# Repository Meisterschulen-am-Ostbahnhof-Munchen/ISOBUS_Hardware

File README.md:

# ISOBUS Hardware

Welcome to the **ISOBUS Hardware** repository by **Meisterschulen am Ostbahnhof, München**. This repository hosts hardware designs for Open Source ISOBUS ECUs.

## 📂 Projects

### [Hutschienenmoped](./Hutschienenmoped)
The **Hutschienenmoped** is an Open Source ISOBUS ECU designed for DIN rail mounting.

* **📂 Source Code:** [View Directory](./Hutschienenmoped)
* **📖 Documentation:** [Read the Docs](https://install-isobus-environment-docs.readthedocs.io/de/latest/HutschienenMoped.html)

---

### [Hutschienenmoped XL](./Hutschienenmoped-XL)
The **Hutschienenmoped XL** is an extended version of the Open Source ISOBUS ECU.

* **📂 Source Code:** [View Directory](./Hutschienenmoped-XL)
* **🏅 Open Hardware:** Certified under [DE000145](https://certification.oshwa.org/de000145.html)

## 📜 License

This project is licensed under a **Creative Commons Attribution-ShareAlike 4.0 International License (CC BY-SA 4.0)**.

* **Hutschienenmoped** by Meisterschulen am Ostbahnhof, München
* **ISOBUS_Hardware** by Meisterschulen am Ostbahnhof, München

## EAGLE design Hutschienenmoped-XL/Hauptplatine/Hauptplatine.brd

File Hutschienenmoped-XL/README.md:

# Hutschienenmoped XL

Das **Hutschienenmoped XL** ist ein innovatives Gerät, das speziell für die Integration in ISOBUS-Systeme entwickelt wurde. Es handelt sich dabei um eine Open-Source-ECU (Electronic Control Unit), die mit den Standards **ISO 11783** und **IEC 61499** kompatibel ist. Diese Kompatibilität ermöglicht eine nahtlose Kommunikation und Steuerung von landwirtschaftlichen Maschinen und Anbaugeräten.

### Vorteile
* **Flexibilität:** Durch die Open-Source-Natur des Projekts können Benutzer die Software und Hardware nach ihren Bedürfnissen anpassen und erweitern.
* **Kompatibilität:** Es unterstützt eine Vielzahl von ISOBUS-kompatiblen Geräten, was die Integration in bestehende Systeme erleichtert.
* **Zukunftssicherheit:** Dank der Einhaltung internationaler Standards ist das Gerät zukunftssicher und kann in verschiedenen landwirtschaftlichen Anwendungen eingesetzt werden.

---

## 🛠 CAD & 3D-Design (Fusion 360)

Das Projekt wird derzeit in Fusion 360 migriert. Hier finden Sie die aktuellen Modelle:

* 🔌 **[Hauptplatine (PCB)](https://a360.co/3YcFeBx)**
* 📦 **[Zusammenbau (Assembly)](https://a360.co/4cJ5Ajy)**

### Galerie

---

## 📜 Lizenz

Dieses Projekt ist lizenziert unter einer **Creative Commons Attribution-ShareAlike 4.0 International License (CC BY-SA 4.0)**.

* **Urheber:** [Meisterschulen am Ostbahnhof, München](https://github.com/Meisterschulen-am-Ostbahnhof-Munchen)
* **Projekt:** [Hutschienenmoped](https://github.com/Meisterschulen-am-Ostbahnhof-Munchen/ISOBUS_Hardware)

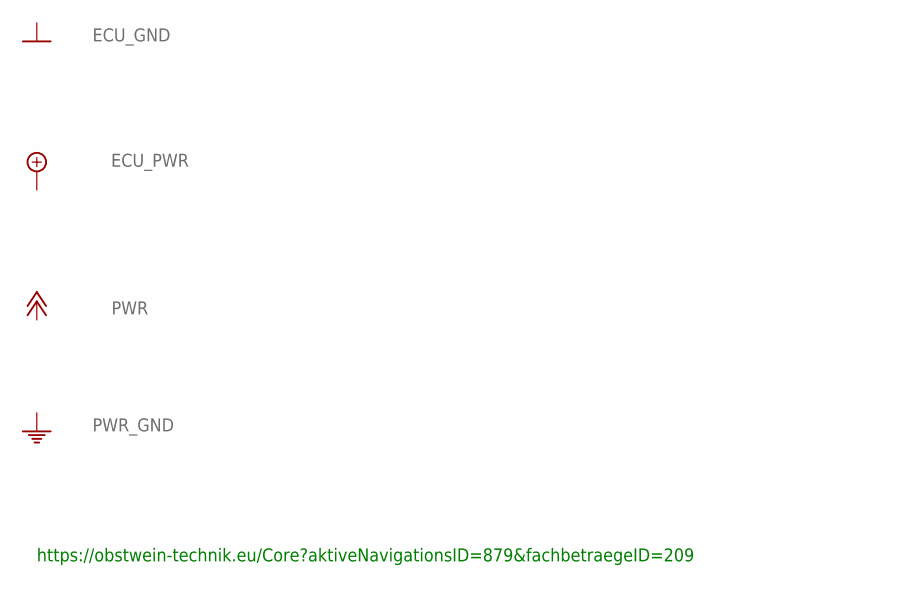
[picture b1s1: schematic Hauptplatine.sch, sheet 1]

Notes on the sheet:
https://obstwein-technik.eu/Core?aktiveNavigationsID=879&fachbetraegeID=209

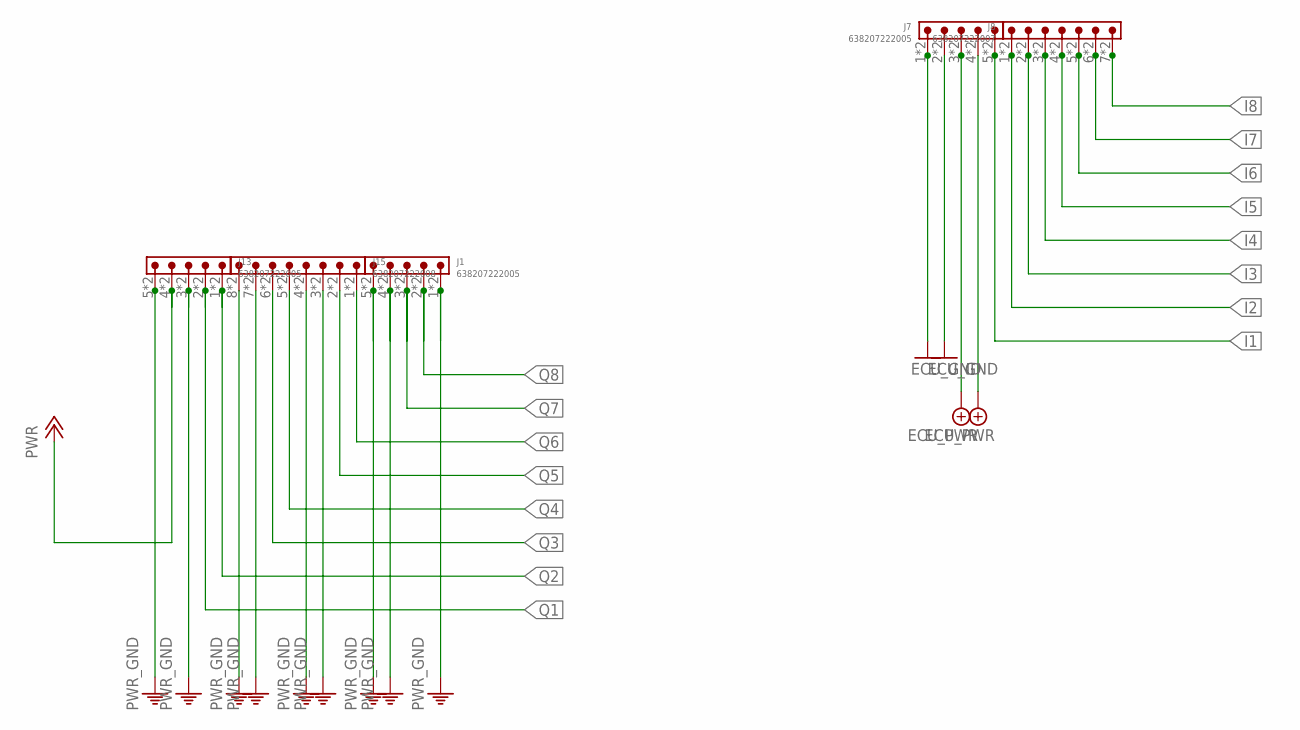
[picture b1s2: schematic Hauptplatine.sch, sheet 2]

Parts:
J1, J7, J13: 638207222005
J8: 638207222007
J15: 638207222008

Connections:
ECU_GND: J7.1, J7.2, J7.A1 (1), J7.A2 (2); also elsewhere on the board
ECU_PWR: J7.3, J7.4, J7.A3 (3), J7.A4 (4); also elsewhere on the board
I1: J7.5, J7.A5 (5); also elsewhere on the board
I2: J8.1, J8.A1 (1); also elsewhere on the board
I3: J8.2, J8.A2 (2); also elsewhere on the board
I4: J8.3, J8.A3 (3); also elsewhere on the board
I5: J8.4, J8.A4 (4); also elsewhere on the board
I6: J8.5, J8.A5 (5); also elsewhere on the board
I7: J8.6, J8.A6 (6); also elsewhere on the board
I8: J8.7, J8.A7 (7); also elsewhere on the board
PWR: J13.4, J13.A4 (4); also elsewhere on the board
PWR_GND: J1.1, J1.4, J1.5, J1.A1 (1), J1.A4 (4), J1.A5 (5), J13.3, J13.5, J13.A3 (3), J13.A5 (5), J15.3, J15.4, J15.7, J15.8, J15.A3 (3), J15.A4 (4), J15.A7 (7), J15.A8 (8); also elsewhere on the board
Q1: J13.2, J13.A2 (2); also elsewhere on the board
Q2: J13.1, J13.A1 (1); also elsewhere on the board
Q3: J15.6, J15.A6 (6); also elsewhere on the board
Q4: J15.5, J15.A5 (5); also elsewhere on the board
Q5: J15.2, J15.A2 (2); also elsewhere on the board
Q6: J15.1, J15.A1 (1); also elsewhere on the board
Q7: J1.3, J1.A3 (3); also elsewhere on the board
Q8: J1.2, J1.A2 (2); also elsewhere on the board

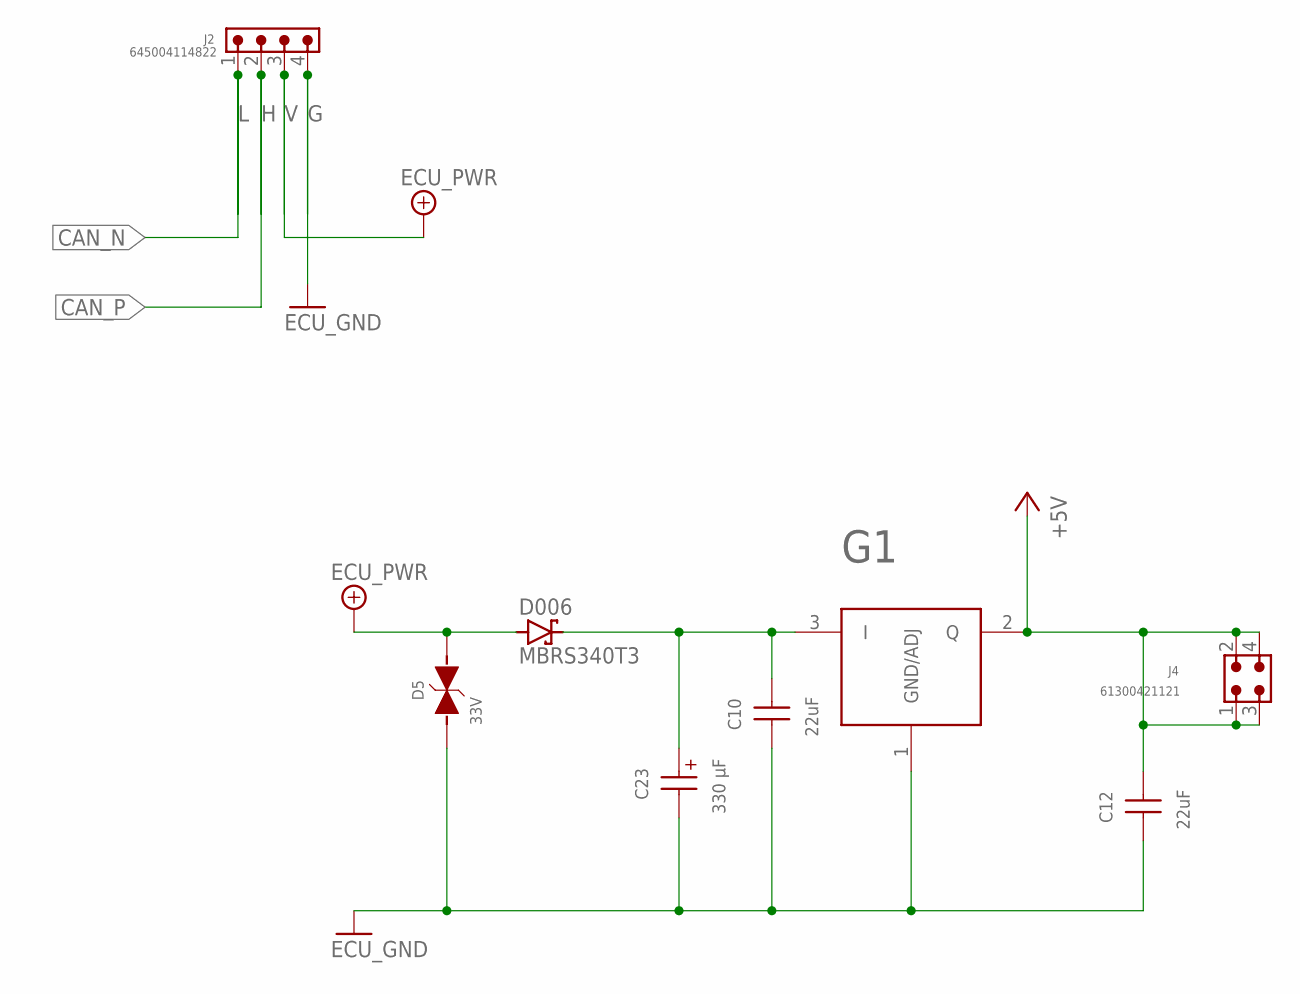
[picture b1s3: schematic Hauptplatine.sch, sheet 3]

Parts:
C10: 22uF; WCAP-CSGP_1210_H2.5
C12: 22uF; WCAP-CSGP_0805_H1.25_R
C23: 330 µF; WCAP-ASLI_12.5X14(DXL)
D5: 33V; WE-TVSP_DO-214AB_BIDIRECTIONAL
D006: MBRS340T3; SMC
G1: IFX27001TF_V50; INF-PG-TO252-3-11_N
J2: 645004114822
J4: 61300421121

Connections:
+5V: C12.2, G1.2 (Q), J4.1, J4.2, J4.3, J4.4; also elsewhere on the board
CAN_N: J2.1; also elsewhere on the board
CAN_P: J2.2; also elsewhere on the board
ECU_GND: C10.1, C12.1, C23.2 (-), D5.1, G1.1 (GND/ADJ), J2.4; also elsewhere on the board
ECU_PWR: D5.2, D006.A, J2.3; also elsewhere on the board
unnamed: C10.2, C23.1 (+), D006.C, G1.3 (I)

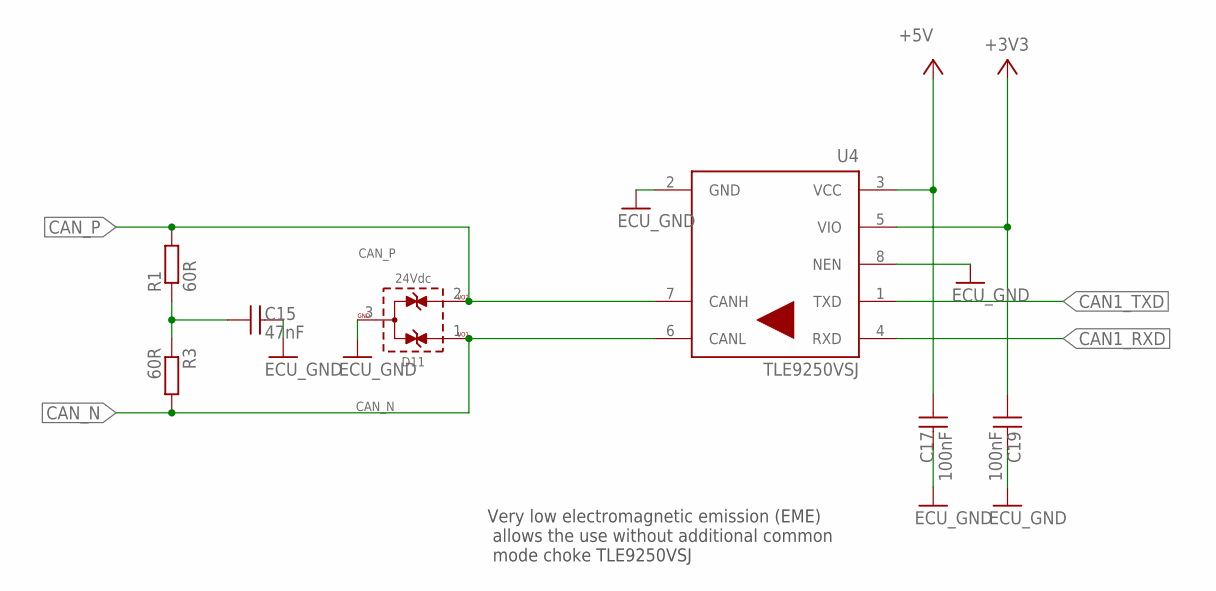
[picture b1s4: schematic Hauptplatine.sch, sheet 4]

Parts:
C15: 47nF; WCAP-CSGP_0805_H0.8_R
C17, C19: 100nF; WCAP-CSGP_0805_H0.8_R
D11: 24Vdc; WE-TVS_SOT23-3L
R1, R3: 60R; R0805
U4: TLE9250VSJ; SOIC127P602X173-8N-V

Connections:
+3V3: C19.1, U4.5 (VIO); also elsewhere on the board
+5V: C17.1, U4.3 (VCC); also elsewhere on the board
CAN1_RXD: U4.4 (RXD); also elsewhere on the board
CAN1_TXD: U4.1 (TXD); also elsewhere on the board
CAN_N: D11.1 (I/O1), R3.2, U4.6 (CANL); also elsewhere on the board
CAN_P: D11.2 (I/O2), R1.2, U4.7 (CANH); also elsewhere on the board
ECU_GND: C15.2, C17.2, C19.2, D11.3 (GND), U4.2 (GND), U4.8 (NEN); also elsewhere on the board
unnamed: C15.1, R1.1, R3.1

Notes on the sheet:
Very low electromagnetic emission (EME) allows the use without additional common mode choke TLE9250VSJ

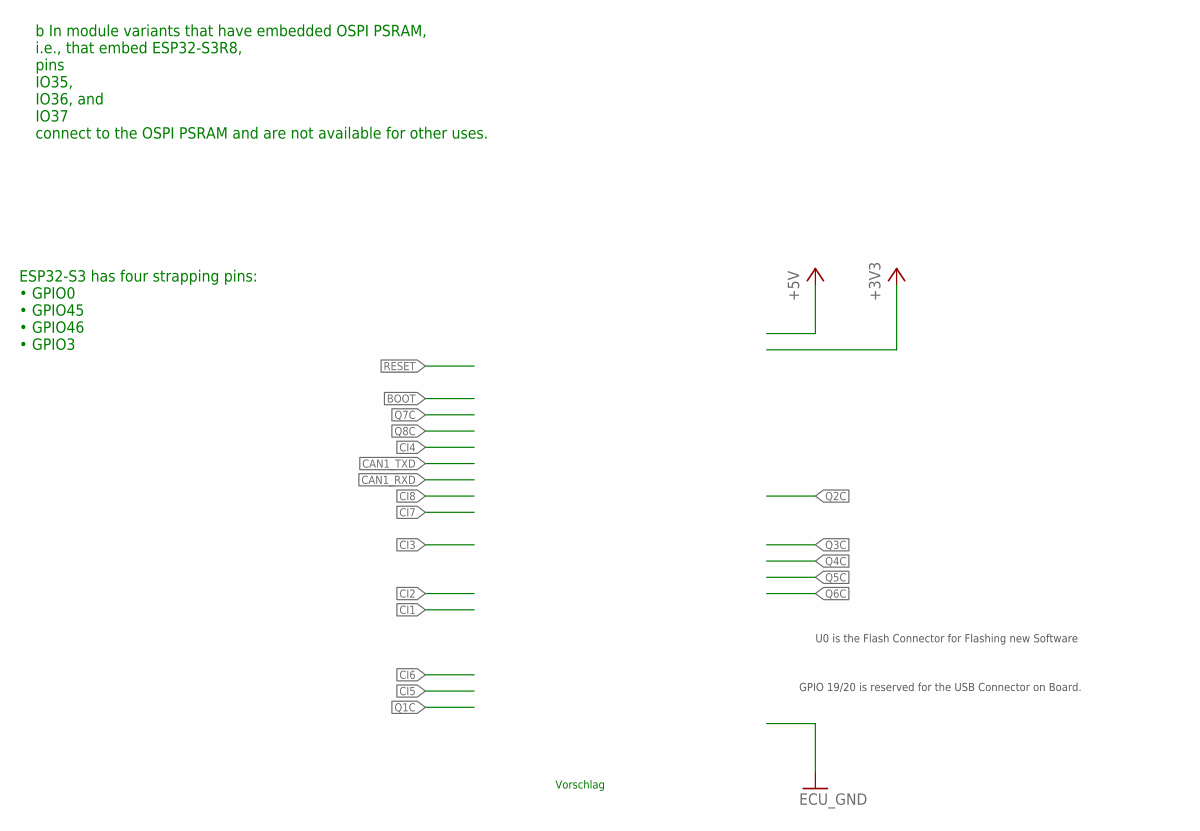
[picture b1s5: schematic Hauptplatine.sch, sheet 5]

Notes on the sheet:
Vorschlag
ESP32-S3 has four strapping pins: • GPIO0 • GPIO45 • GPIO46 • GPIO3
b In module variants that have embedded OSPI PSRAM, i.e., that embed ESP32-S3R8, pins IO35, IO36, and IO37 connect to the OSPI PSRAM and are not available for other uses.
GPIO 19/20 is reserved for the USB Connector on Board.
U0 is the Flash Connector for Flashing new Software

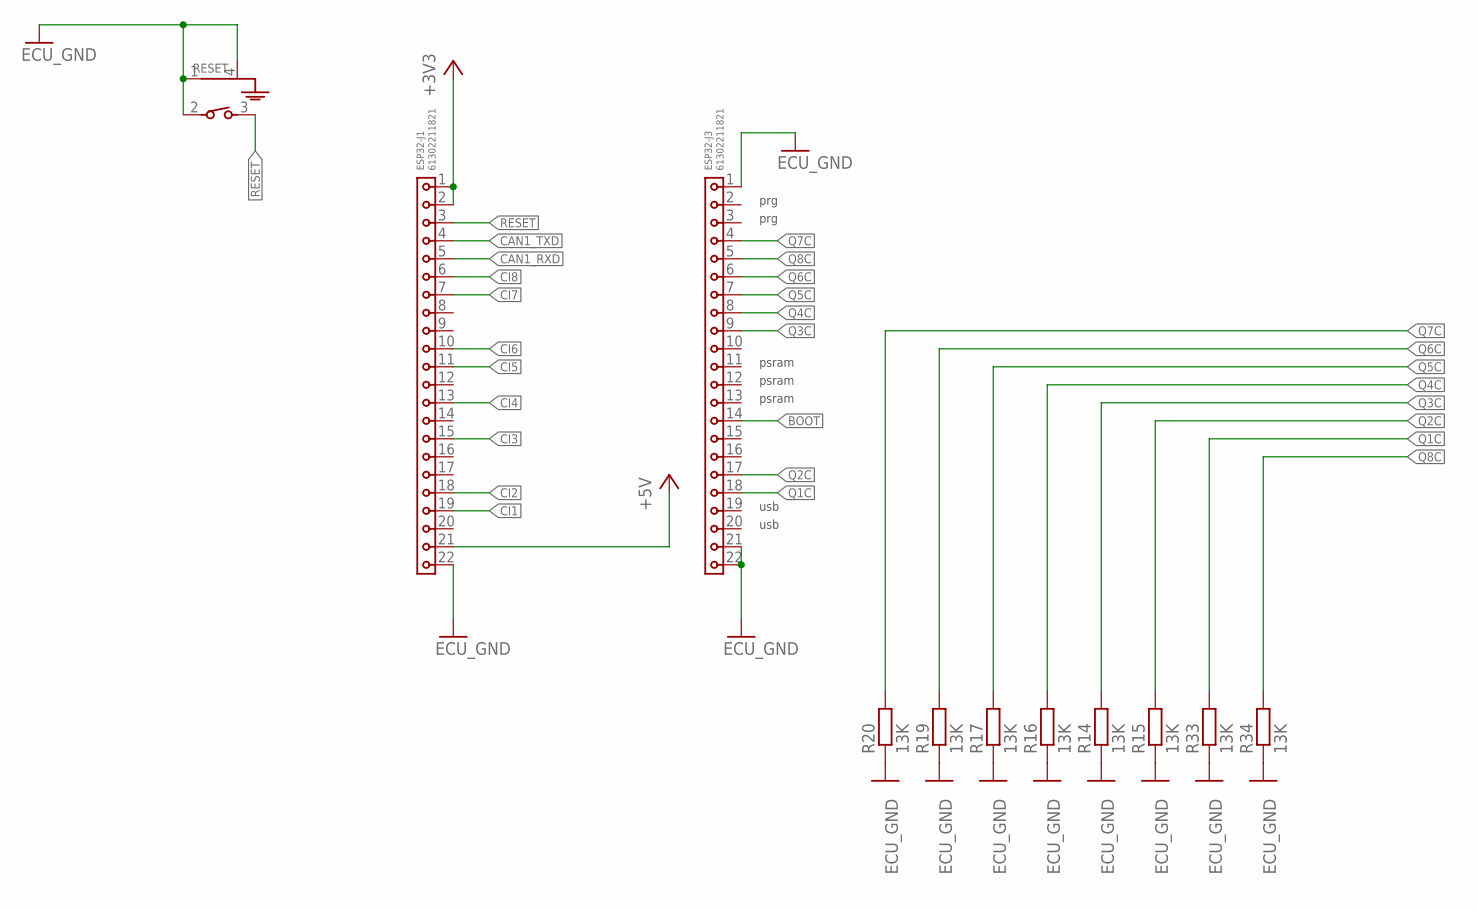
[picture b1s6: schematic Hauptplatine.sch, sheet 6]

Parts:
ESP32-J1, ESP32-J3: 61302211821
R14, R15, R16, R17, R19, R20, R33, R34: 13K; R1206
RESET: 431256083736; 4312560837X6

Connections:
+3V3: ESP32-J1.1, ESP32-J1.2; also elsewhere on the board
+5V: ESP32-J1.21; also elsewhere on the board
BOOT: ESP32-J3.14
CAN1_RXD: ESP32-J1.5; also elsewhere on the board
CAN1_TXD: ESP32-J1.4; also elsewhere on the board
CI1: ESP32-J1.19; also elsewhere on the board
CI2: ESP32-J1.18; also elsewhere on the board
CI3: ESP32-J1.15; also elsewhere on the board
CI4: ESP32-J1.13; also elsewhere on the board
CI5: ESP32-J1.11; also elsewhere on the board
CI6: ESP32-J1.10; also elsewhere on the board
CI7: ESP32-J1.7; also elsewhere on the board
CI8: ESP32-J1.6; also elsewhere on the board
ECU_GND: ESP32-J1.22, ESP32-J3.1, ESP32-J3.21, ESP32-J3.22, R14.1, R15.1, R16.1, R17.1, R19.1, R20.1, R33.1, R34.1, RESET.1 (GND1), RESET.2, RESET.4 (GND); also elsewhere on the board
Q1C: ESP32-J3.18, R33.2; also elsewhere on the board
Q2C: ESP32-J3.17, R15.2; also elsewhere on the board
Q3C: ESP32-J3.9, R14.2; also elsewhere on the board
Q4C: ESP32-J3.8, R16.2; also elsewhere on the board
Q5C: ESP32-J3.7, R17.2; also elsewhere on the board
Q6C: ESP32-J3.6, R19.2; also elsewhere on the board
Q7C: ESP32-J3.4, R20.2; also elsewhere on the board
Q8C: ESP32-J3.5, R34.2; also elsewhere on the board
RESET: ESP32-J1.3, RESET.3

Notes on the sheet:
usb
prg
psram

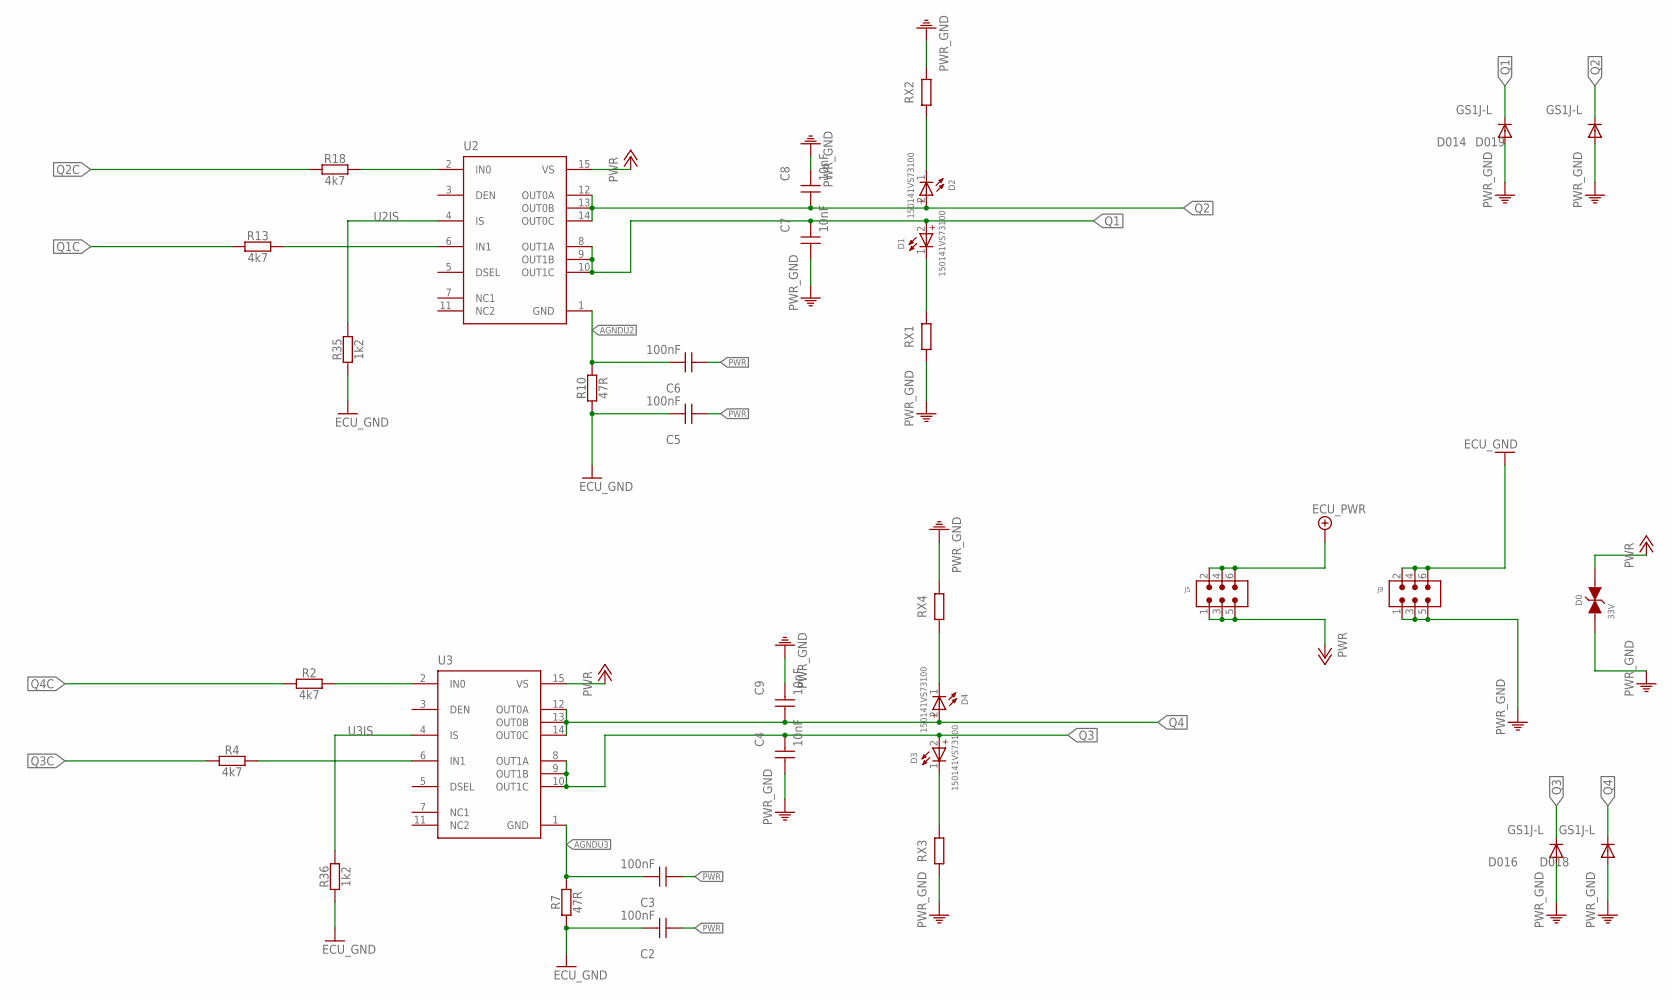
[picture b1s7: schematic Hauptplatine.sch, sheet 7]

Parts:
C2, C3, C5, C6: 100nF; WCAP-CSGP_0805_H0.8_R
C4, C7, C8, C9: 10nF; WCAP-CSGP_0805_H0.8_R
D0: 33V; WE-TVSP_DO-214AB_BIDIRECTIONAL
D1, D2, D3, D4: 150141VS73100; WL-SMTW_3528
D014, D016, D018, D019: GS1J-L; SMA_DO-214AC
J5, J9: 6130XX21121_61300621121; 61300621121
R2, R4, R13, R18: 4k7; R0805
R7, R10: 47R; R0805
R35, R36: 1k2; R0805
RX1, RX2, RX3, RX4: 470Ohm; R1206
U2, U3: BTS7030-2EPA; SOP65P600X115-15N-V

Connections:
AGNDU2: C6.2, R10.2, U2.1 (GND)
AGNDU3: C3.2, R7.2, U3.1 (GND)
ECU_GND: C2.2, C5.2, J9.2, J9.4, J9.6, R7.1, R10.1, R35.1, R36.1; also elsewhere on the board
ECU_PWR: J5.2, J5.4, J5.6; also elsewhere on the board
unnamed: D4.1 (-), RX4.1
unnamed: R2.2, U3.2 (IN0)
unnamed: R4.2, U3.6 (IN1)
unnamed: D2.1 (-), RX2.1
unnamed: D1.1 (-), RX1.2
unnamed: D3.1 (-), RX3.2
unnamed: R18.2, U2.2 (IN0)
unnamed: R13.2, U2.6 (IN1)
PWR: C2.1, C3.1, C5.1, C6.1, D0.2, J5.1, J5.3, J5.5, U2.15 (VS), U3.15 (VS); also elsewhere on the board
PWR_GND: C4.1, C7.1, C8.2, C9.2, D0.1, D014.A, D016.A, D018.A, D019.A, J9.1, J9.3, J9.5, RX1.1, RX2.2, RX3.1, RX4.2; also elsewhere on the board
Q1: C7.2, D1.2 (+), D014.C, U2.8 (OUT1A), U2.9 (OUT1B), U2.10 (OUT1C); also elsewhere on the board
Q1C: R13.1; also elsewhere on the board
Q2: C8.1, D2.2 (+), D019.C, U2.12 (OUT0A), U2.13 (OUT0B), U2.14 (OUT0C); also elsewhere on the board
Q2C: R18.1; also elsewhere on the board
Q3: C4.2, D3.2 (+), D016.C, U3.8 (OUT1A), U3.9 (OUT1B), U3.10 (OUT1C); also elsewhere on the board
Q3C: R4.1; also elsewhere on the board
Q4: C9.1, D4.2 (+), D018.C, U3.12 (OUT0A), U3.13 (OUT0B), U3.14 (OUT0C); also elsewhere on the board
Q4C: R2.1; also elsewhere on the board
U2IS: R35.2, U2.4 (IS)
U3IS: R36.2, U3.4 (IS)

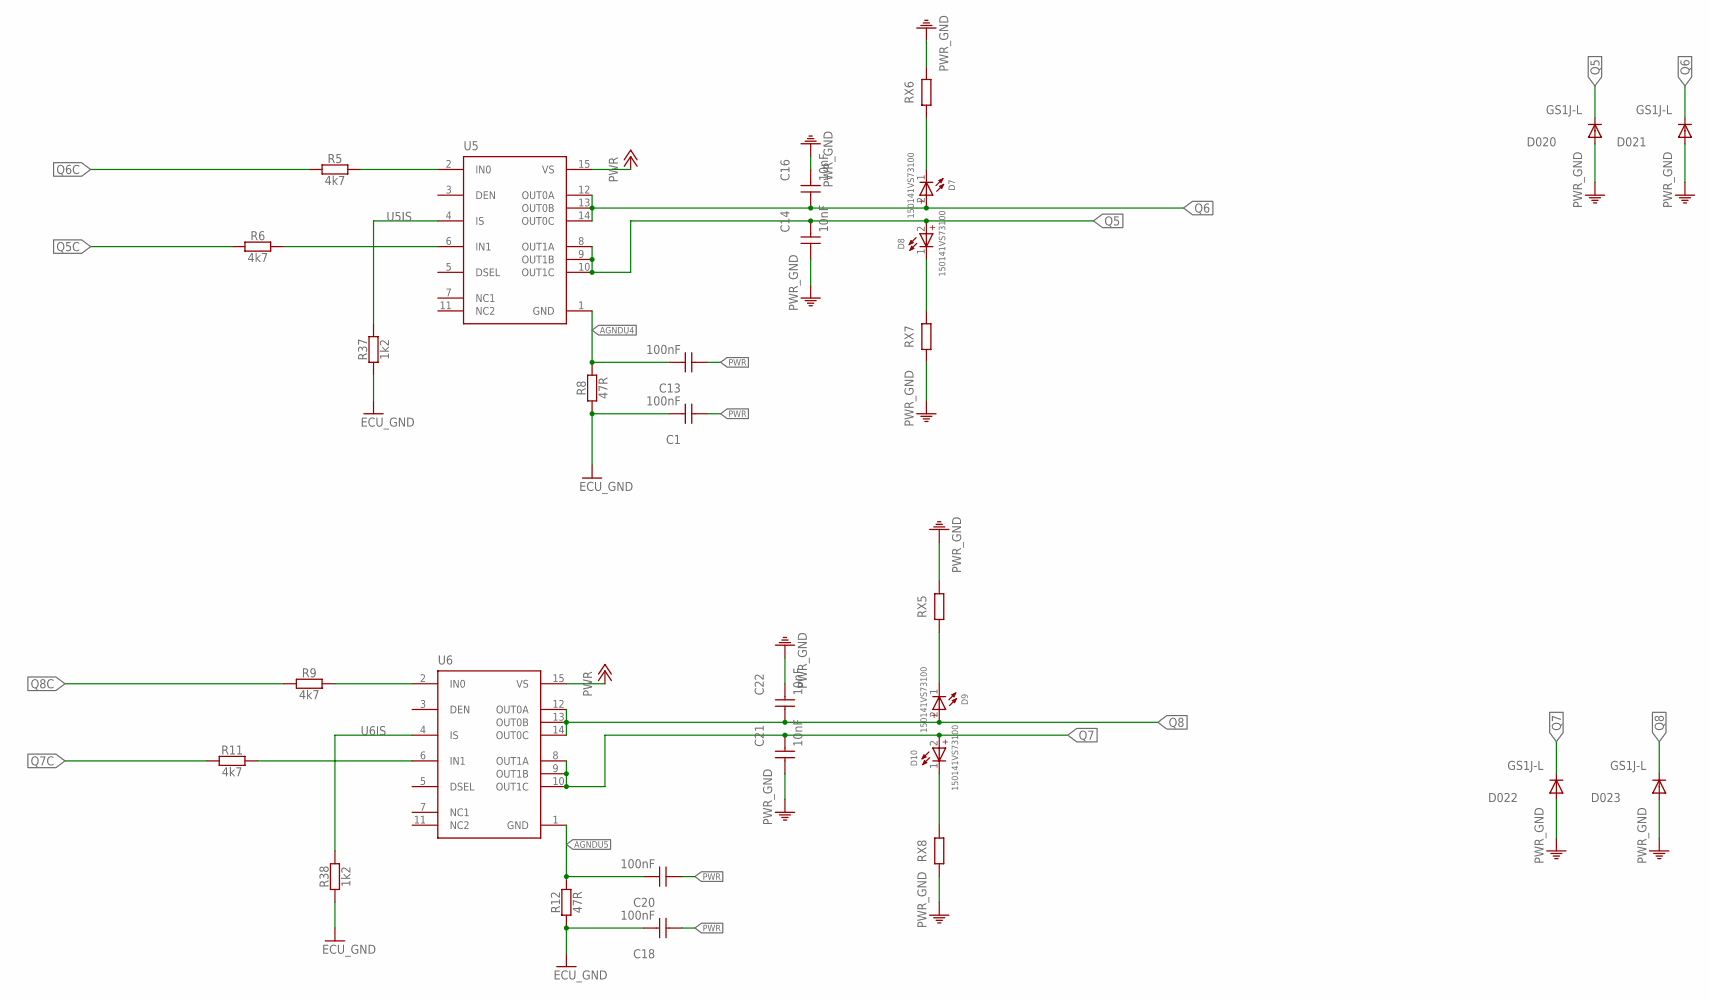
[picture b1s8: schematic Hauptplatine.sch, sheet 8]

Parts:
C1, C13, C18, C20: 100nF; WCAP-CSGP_0805_H0.8_R
C14, C16, C21, C22: 10nF; WCAP-CSGP_0805_H0.8_R
D7, D8, D9, D10: 150141VS73100; WL-SMTW_3528
D020, D021, D022, D023: GS1J-L; SMA_DO-214AC
R5, R6, R9, R11: 4k7; R0805
R8, R12: 47R; R0805
R37, R38: 1k2; R0805
RX5, RX6, RX7, RX8: 470Ohm; R1206
U5, U6: BTS7030-2EPA; SOP65P600X115-15N-V

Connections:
+6V: D7.1 (-), RX6.1
AGNDU4: C13.2, R8.2, U5.1 (GND)
AGNDU5: C20.2, R12.2, U6.1 (GND)
ECU_GND: C1.2, C18.2, R8.1, R12.1, R37.1, R38.1; also elsewhere on the board
unnamed: R5.2, U5.2 (IN0)
unnamed: R6.2, U5.6 (IN1)
unnamed: R9.2, U6.2 (IN0)
unnamed: R11.2, U6.6 (IN1)
unnamed: D9.1 (-), RX5.1
unnamed: D8.1 (-), RX7.2
unnamed: D10.1 (-), RX8.2
PWR: C1.1, C13.1, C18.1, C20.1, U5.15 (VS), U6.15 (VS); also elsewhere on the board
PWR_GND: C14.1, C16.2, C21.1, C22.2, D020.A, D021.A, D022.A, D023.A, RX5.2, RX6.2, RX7.1, RX8.1; also elsewhere on the board
Q5: C14.2, D8.2 (+), D020.C, U5.8 (OUT1A), U5.9 (OUT1B), U5.10 (OUT1C); also elsewhere on the board
Q5C: R6.1; also elsewhere on the board
Q6: C16.1, D7.2 (+), D021.C, U5.12 (OUT0A), U5.13 (OUT0B), U5.14 (OUT0C); also elsewhere on the board
Q6C: R5.1; also elsewhere on the board
Q7: C21.2, D10.2 (+), D022.C, U6.8 (OUT1A), U6.9 (OUT1B), U6.10 (OUT1C); also elsewhere on the board
Q7C: R11.1; also elsewhere on the board
Q8: C22.1, D9.2 (+), D023.C, U6.12 (OUT0A), U6.13 (OUT0B), U6.14 (OUT0C); also elsewhere on the board
Q8C: R9.1; also elsewhere on the board
U5IS: R37.2, U5.4 (IS)
U6IS: R38.2, U6.4 (IS)

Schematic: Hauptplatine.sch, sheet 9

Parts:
C31, C32, C33, C34: 100nF; WCAP-CSGP_1206_H0.8
D13: 3.3Vdc; WE-TVS_SOT143-4L
R21, R24: 1K2; R1206
R22, R25: 47K; R1206
R23, R26: 22K; R1206

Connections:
+3V3: D13.4 (VDD); also elsewhere on the board
CI1: C32.1, D13.3 (2), R22.1, R23.2; also elsewhere on the board
CI2: C34.1, D13.2 (1), R25.1, R26.2; also elsewhere on the board
ECU_GND: C31.2, C32.2, C33.2, C34.2, D13.1 (GND), R21.1, R23.1, R24.1, R26.1; also elsewhere on the board
I1: C31.1, R21.2, R22.2; also elsewhere on the board
I2: C33.1, R24.2, R25.2; also elsewhere on the board

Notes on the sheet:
Symbol Parameter Min Typ Max Unit CIN Pin capacitance - 2 - pF VIH High-level input voltage 0.75×VDD1 - VDD1+0.3 V (‭2,475‬V - 3.6V) VIL Low-level input voltage –0.3 - 0.25×VDD1 V (-0,3 - ‭0,825‬V)
2.6V bei 12V 3.07 bei 14.2V

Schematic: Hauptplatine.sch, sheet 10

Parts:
C39, C40, C41, C42: 100nF; WCAP-CSGP_1206_H0.8
D15: 3.3Vdc; WE-TVS_SOT143-4L
R39, R42: 1K2; R1206
R40, R43: 47K; R1206
R41, R44: 22K; R1206

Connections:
+3V3: D15.4 (VDD); also elsewhere on the board
CI3: C40.1, D15.3 (2), R40.1, R41.2; also elsewhere on the board
CI4: C42.1, D15.2 (1), R43.1, R44.2; also elsewhere on the board
ECU_GND: C39.2, C40.2, C41.2, C42.2, D15.1 (GND), R39.1, R41.1, R42.1, R44.1; also elsewhere on the board
I3: C39.1, R39.2, R40.2; also elsewhere on the board
I4: C41.1, R42.2, R43.2; also elsewhere on the board

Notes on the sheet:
Symbol Parameter Min Typ Max Unit CIN Pin capacitance - 2 - pF VIH High-level input voltage 0.75×VDD1 - VDD1+0.3 V (‭2,475‬V - 3.6V) VIL Low-level input voltage –0.3 - 0.25×VDD1 V (-0,3 - ‭0,825‬V)
2.6V bei 12V 3.07 bei 14.2V

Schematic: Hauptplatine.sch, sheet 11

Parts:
C47, C48, C49, C50: 100nF; WCAP-CSGP_1206_H0.8
D17: 3.3Vdc; WE-TVS_SOT143-4L
R51, R54: 1K2; R1206
R52, R55: 47K; R1206
R53, R56: 22K; R1206

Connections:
+3V3: D17.4 (VDD); also elsewhere on the board
CI5: C48.1, D17.3 (2), R52.1, R53.2; also elsewhere on the board
CI6: C50.1, D17.2 (1), R55.1, R56.2; also elsewhere on the board
ECU_GND: C47.2, C48.2, C49.2, C50.2, D17.1 (GND), R51.1, R53.1, R54.1, R56.1; also elsewhere on the board
I5: C47.1, R51.2, R52.2; also elsewhere on the board
I6: C49.1, R54.2, R55.2; also elsewhere on the board

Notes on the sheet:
Symbol Parameter Min Typ Max Unit CIN Pin capacitance - 2 - pF VIH High-level input voltage 0.75×VDD1 - VDD1+0.3 V (‭2,475‬V - 3.6V) VIL Low-level input voltage –0.3 - 0.25×VDD1 V (-0,3 - ‭0,825‬V)
2.6V bei 12V 3.07 bei 14.2V

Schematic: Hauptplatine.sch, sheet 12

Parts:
C24, C25, C26, C27: 100nF; WCAP-CSGP_1206_H0.8
D12: 3.3Vdc; WE-TVS_SOT143-4L
R27, R28: 1K2; R1206
R29, R30: 47K; R1206
R31, R32: 22K; R1206

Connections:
+3V3: D12.4 (VDD); also elsewhere on the board
CI7: C27.1, D12.3 (2), R30.1, R32.2; also elsewhere on the board
CI8: C26.1, D12.2 (1), R29.1, R31.2; also elsewhere on the board
ECU_GND: C24.2, C25.2, C26.2, C27.2, D12.1 (GND), R27.1, R28.1, R31.1, R32.1; also elsewhere on the board
I7: C25.1, R28.2, R30.2; also elsewhere on the board
I8: C24.1, R27.2, R29.2; also elsewhere on the board

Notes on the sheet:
Symbol Parameter Min Typ Max Unit CIN Pin capacitance - 2 - pF VIH High-level input voltage 0.75×VDD1 - VDD1+0.3 V (‭2,475‬V - 3.6V) VIL Low-level input voltage –0.3 - 0.25×VDD1 V (-0,3 - ‭0,825‬V)
2.6V bei 12V 3.07 bei 14.2V

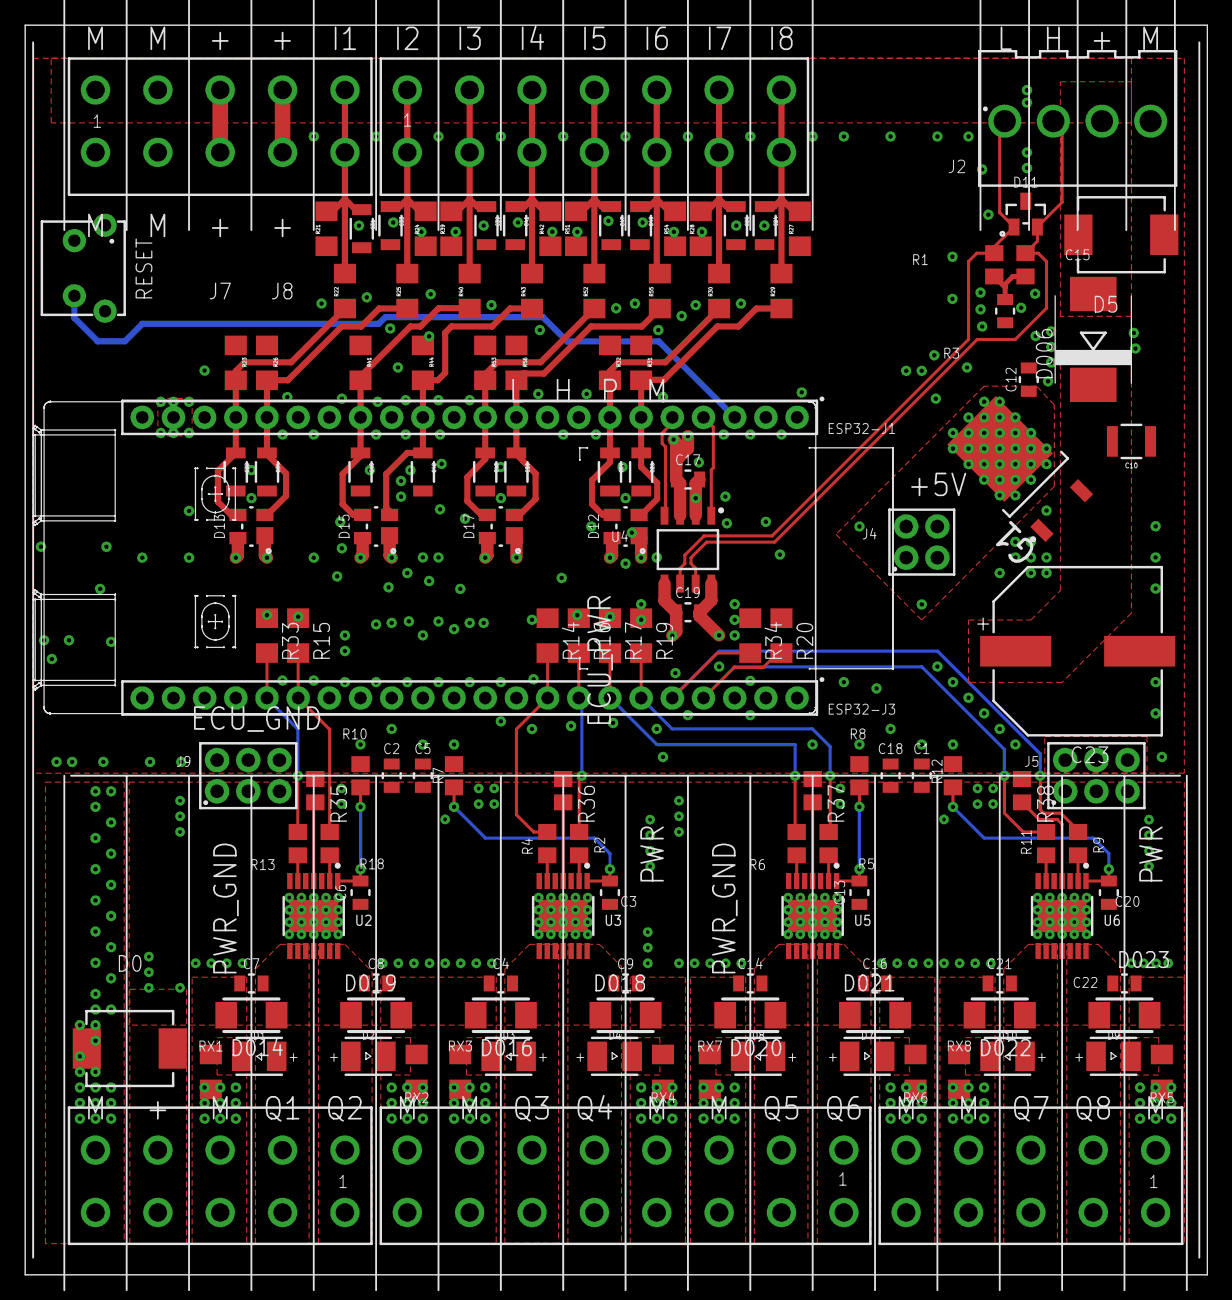
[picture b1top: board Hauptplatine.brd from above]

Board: 4 copper layers, 96.3 x 101.8 mm, 138 parts (0 on the bottom side), 69 nets.

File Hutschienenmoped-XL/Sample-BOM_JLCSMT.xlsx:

Comment | Designator | Footprint | JLCPCB Part #（optional）
431256083736 | RESET | 4312560837X6
6130XX21121_61300621121 | J5, J9 | 61300621121
BTS7030-2EPA | U2, U3, U5, U6 | SOP65P600X115-15N-V
IFX27001TF_V50 | G1 | INF-PG-TO252-3-11_N
61300421121 | J4 | 61300421121
61302211821 | ESP32-J1, ESP32-J3 | 61302211821
638207222005 | J1, J7, J13 | 638207222005
638207222007 | J8 | 638207222007
638207222008 | J15 | 638207222008
100nF | C1, C2, C3, C5, C6, C13, C17, C18, C19, C20 | WCAP-CSGP_0805_H0.8_R
100nF | C24, C25, C26, C27, C31, C32, C33, C34, C39, C40, C41, C42, C47, C48, C49, C50 | WCAP-CSGP_1206_H0.8
10nF | C4, C7, C8, C9, C14, C16, C21, C22 | WCAP-CSGP_0805_H0.8_R
13K | R14, R15, R16, R17, R19, R20, R23, R26, R31, R32, R33, R34, R41, R44, R53, R56 | R1206
150141VS73100 | D1, D2, D3, D4, D7, D8, D9, D10 | WL-SMTW_3528
1K2 | R21, R24, R27, R28, R39, R42, R51, R54 | R1206
1k2 | R35, R36, R37, R38 | R0805
22uF | C12 | WCAP-CSGP_0805_H1.25_R
22uF | C10 | WCAP-CSGP_1210_H2.5
24Vdc | D11 | WE-TVS_SOT23-3L
3.3Vdc | D12, D13, D15, D17 | WE-TVS_SOT143-4L
330 ÂµF | C23 | WCAP-ASLI_12.5X14(DXL)
33V | D0, D5 | WE-TVSP_DO-214AB_BIDIRECTIONAL
470Ohm | RX1, RX2, RX3, RX4, RX5, RX6, RX7, RX8 | R1206
47K | R22, R25, R29, R30, R40, R43, R52, R55 | R1206
47R | R7, R8, R10, R12 | R0805
47nF | C15 | WCAP-CSGP_0805_H0.8_R
4k7 | R2, R4, R5, R6, R9, R11, R13, R18 | R0805
60R | R1, R3 | R0805
645004114822 | J2 | 645004114822
GS1J-L | D014, D016, D018, D019, D020, D021, D022, D023 | SMA_DO-214AC
MBRS340T3 | D006 | SMC
TLE9250VSJ | U4 | SOIC127P602X173-8N-V

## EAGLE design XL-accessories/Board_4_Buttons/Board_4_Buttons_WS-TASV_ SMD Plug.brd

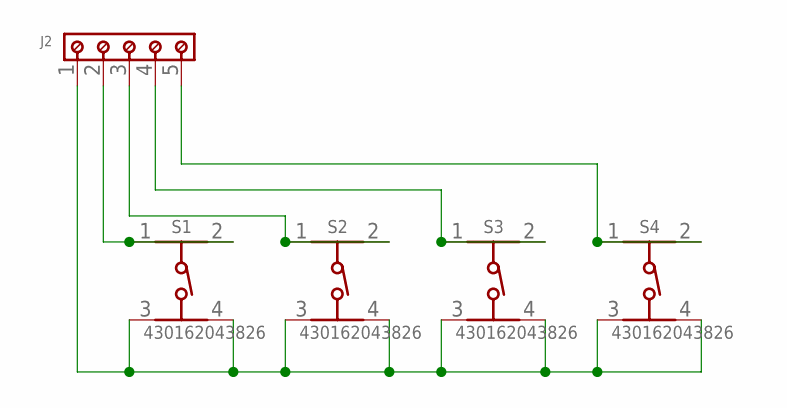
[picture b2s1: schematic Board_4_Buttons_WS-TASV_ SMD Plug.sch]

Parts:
J2: 691709710305
S1, S2, S3, S4: 430162043826

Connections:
unnamed: J2.1, S1.3 (2), S1.4, S2.3 (2), S2.4, S3.3 (2), S3.4, S4.3 (2), S4.4
unnamed: J2.2, S1.1, S1.2 (3)
unnamed: J2.3, S2.1, S2.2 (3)
unnamed: J2.4, S3.1, S3.2 (3)
unnamed: J2.5, S4.1, S4.2 (3)

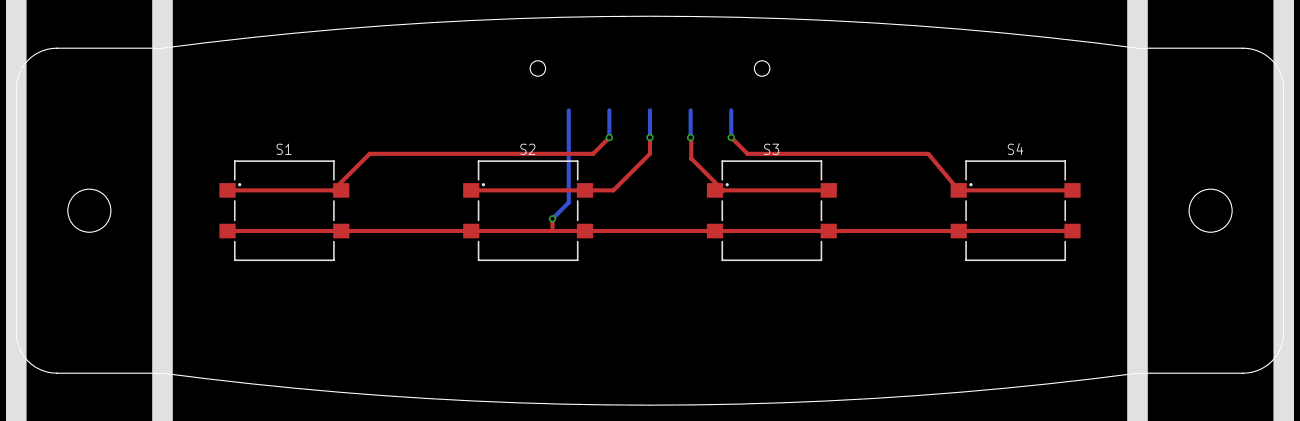
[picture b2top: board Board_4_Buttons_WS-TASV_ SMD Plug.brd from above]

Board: 2 copper layers, 156.0 x 47.9 mm, 5 parts (1 on the bottom side), 5 nets.

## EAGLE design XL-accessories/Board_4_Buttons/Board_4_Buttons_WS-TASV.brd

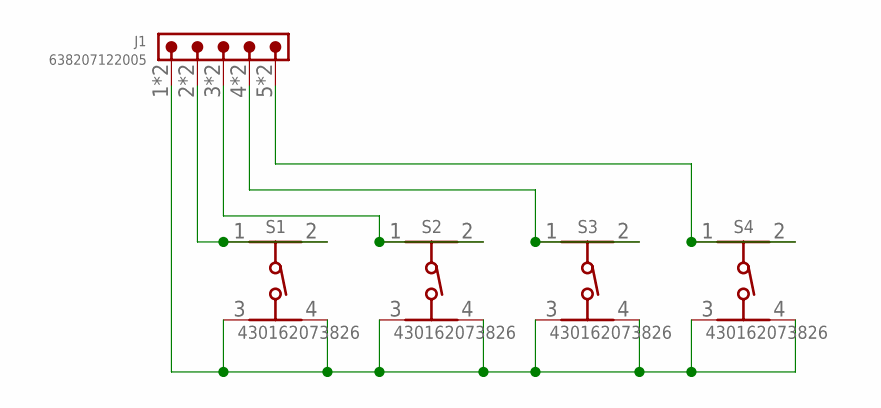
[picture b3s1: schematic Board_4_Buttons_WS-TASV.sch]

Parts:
J1: 638207122005
S1, S2, S3, S4: 430162073826

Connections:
unnamed: J1.1, J1.A1 (1), S1.3 (2), S1.4, S2.3 (2), S2.4, S3.3 (2), S3.4, S4.3 (2), S4.4
unnamed: J1.2, J1.A2 (2), S1.1, S1.2 (3)
unnamed: J1.3, J1.A3 (3), S2.1, S2.2 (3)
unnamed: J1.4, J1.A4 (4), S3.1, S3.2 (3)
unnamed: J1.5, J1.A5 (5), S4.1, S4.2 (3)

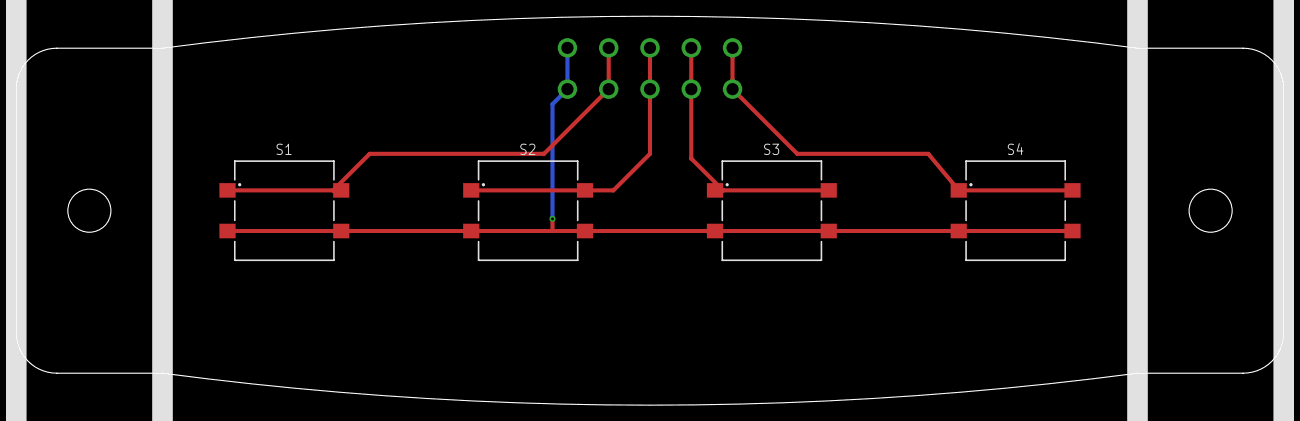
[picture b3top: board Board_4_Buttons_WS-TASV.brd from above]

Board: 2 copper layers, 156.0 x 47.9 mm, 5 parts (1 on the bottom side), 5 nets.

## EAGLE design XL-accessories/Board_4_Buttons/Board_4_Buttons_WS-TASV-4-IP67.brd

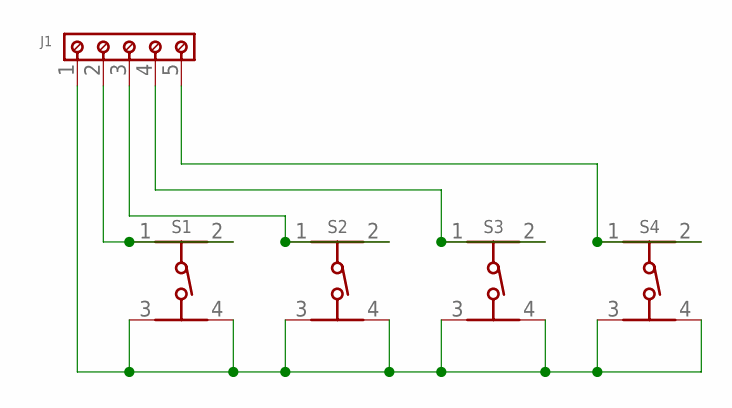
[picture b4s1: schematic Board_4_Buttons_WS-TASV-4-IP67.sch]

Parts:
J1: 691709710305
S1, S2, S3, S4: 430773034825

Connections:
unnamed: J1.1, S1.3 (2), S1.4, S2.3 (2), S2.4, S3.3 (2), S3.4, S4.3 (2), S4.4
unnamed: J1.2, S1.1, S1.2 (3)
unnamed: J1.3, S2.1, S2.2 (3)
unnamed: J1.4, S3.1, S3.2 (3)
unnamed: J1.5, S4.1, S4.2 (3)

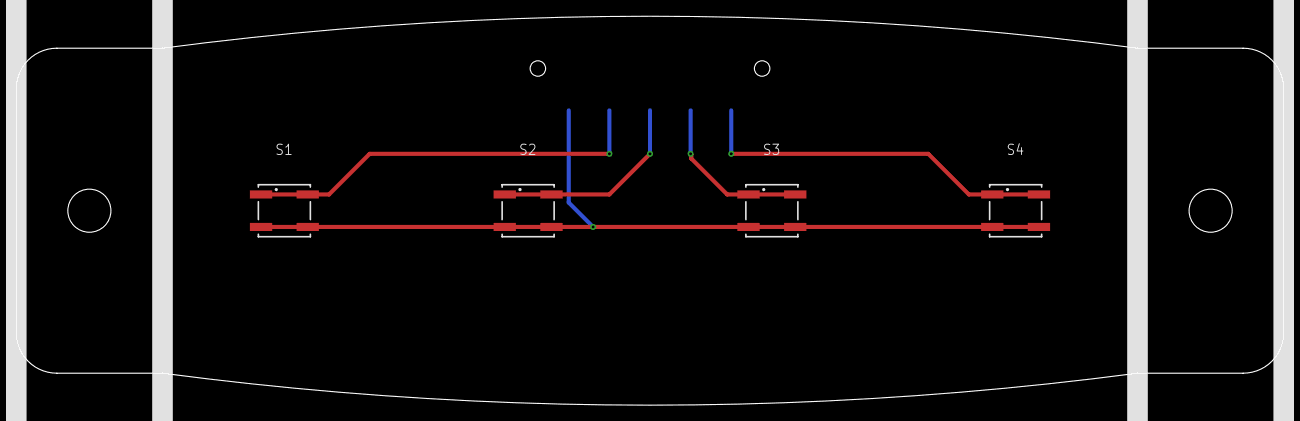
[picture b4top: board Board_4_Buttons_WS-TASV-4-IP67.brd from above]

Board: 2 copper layers, 156.0 x 47.9 mm, 5 parts (1 on the bottom side), 5 nets.

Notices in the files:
parts and their libraries:
Wurth_EMC Components_WE-TVSP: Copyright: Würth Elektronik
